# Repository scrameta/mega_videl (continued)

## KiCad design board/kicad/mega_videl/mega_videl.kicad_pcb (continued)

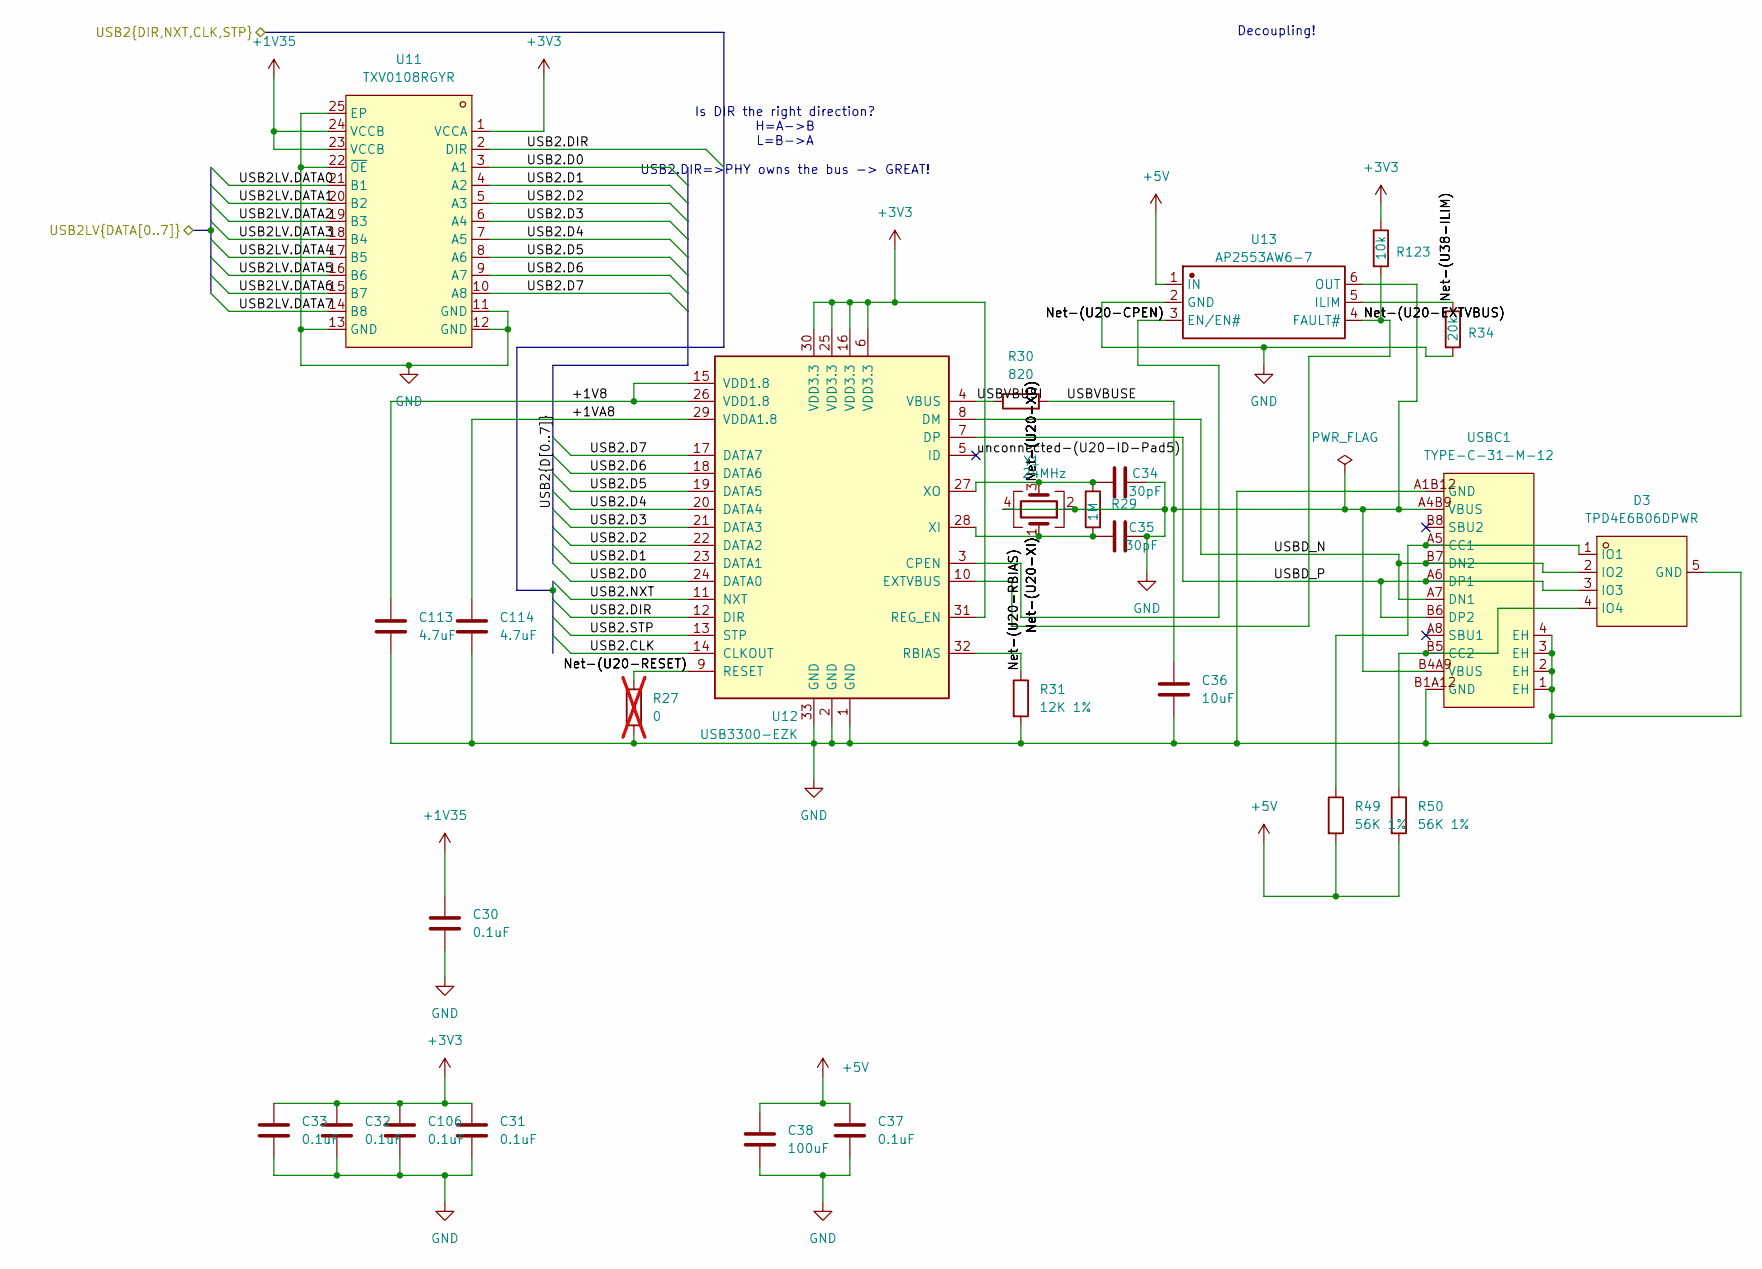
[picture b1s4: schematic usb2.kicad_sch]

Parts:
C30, C31, C32, C33, C37, C106: 0.1uF; C_0603_1608Metric; LCSC C14663
C34, C35: 30pF; C_0603_1608Metric; LCSC C1658
C36: 10uF; C_0805_2012Metric; LCSC C15850
C38: 100uF; C_1206_3216Metric; LCSC C7432784
C113, C114: 4.7uF; C_0805_2012Metric; LCSC C1779
D3: TPD4E6B06DPWR; X2SON-4_L0.8-W0.8-P0.48-TL-A; MPN TPD4E6B06DPWR; LCSC Part C2869397
R27: 0; R_0603_1608Metric; LCSC C21189; not fitted
R29: 1M; R_0603_1608Metric; LCSC C22935
R30: 820; R_0603_1608Metric; LCSC C23253
R31: 12K 1%; R_0603_1608Metric; LCSC C22790
R34: 20k; R_0603_1608Metric; LCSC C4184
R49, R50: 56K 1%; R_0603_1608Metric; LCSC C23206
R123: 10k; R_0603_1608Metric; LCSC C25804
U11: TXV0108RGYR; TQFN-24_L5.5-W3.5-P0.50-BR-EP; MPN TXV0108RGYR; LCSC Part C22428389
U12: USB3300-EZK; QFN-32-1EP_5x5mm_P0.5mm_EP3.45x3.45mm; LCSC C108383
U13: AP2553AW6-7; SOT-26_L3.0-W1.6-P0.95-LS2.8-BL; Manufacturer Part AP2553AW6-7; JLC_3DModel df0aaac1b0f04609b13717eddf3d6f89
USBC1: TYPE-C-31-M-12; USB-C_SMD-TYPE-C-31-M-12_1; MPN TYPE-C-31-M-12; LCSC Part C165948
Y1: 24MHz; Crystal_SMD_3225-4Pin_3.2x2.5mm; LCSC C5308006

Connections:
+1V35: C30.1, U11.23 (VCCB), U11.24 (VCCB); also elsewhere on the board
+3V3: C31.1, C32.1, C33.1, C106.1, R123.1, U11.1 (VCCA), U12.6 (VDD3.3), U12.16 (VDD3.3), U12.25 (VDD3.3), U12.30 (VDD3.3), U12.31 (REG_EN); also elsewhere on the board
+5V: C37.1, C38.1, R49.2, R50.2, U13.1 (IN); also elsewhere on the board
/fpga/USB2.CLK: U12.14 (CLKOUT); also elsewhere on the board
/fpga/USB2.DIR: U11.2 (DIR), U12.12 (DIR); also elsewhere on the board
/fpga/USB2.NXT: U12.11 (NXT); also elsewhere on the board
/fpga/USB2.STP: U12.13 (STP); also elsewhere on the board
/fpga/USB2LV.DATA0: U11.21 (B1); also elsewhere on the board
/fpga/USB2LV.DATA1: U11.20 (B2); also elsewhere on the board
/fpga/USB2LV.DATA2: U11.19 (B3); also elsewhere on the board
/fpga/USB2LV.DATA3: U11.18 (B4); also elsewhere on the board
/fpga/USB2LV.DATA4: U11.17 (B5); also elsewhere on the board
/fpga/USB2LV.DATA5: U11.16 (B6); also elsewhere on the board
/fpga/USB2LV.DATA6: U11.15 (B7); also elsewhere on the board
/fpga/USB2LV.DATA7: U11.14 (B8); also elsewhere on the board
/usb2/+1V8: C113.1, U12.15 (VDD1.8), U12.26 (VDD1.8)
/usb2/+1VA8: C114.1, U12.29 (VDDA1.8)
/usb2/Net-(U20-CPEN): U12.3 (CPEN), U13.3 (EN/EN#)
/usb2/Net-(U20-EXTVBUS): R123.2, U12.10 (EXTVBUS), U13.4 (FAULT#)
/usb2/Net-(U20-RBIAS): R31.1, U12.32 (RBIAS)
/usb2/Net-(U20-RESET): R27.1, U12.9 (RESET)
/usb2/Net-(U20-XI): C35.2, R29.2, U12.28 (XI), Y1.1
/usb2/Net-(U20-XO): C34.2, R29.1, U12.27 (XO), Y1.3
/usb2/Net-(U38-ILIM): R34.1, U13.5 (ILIM)
/usb2/USB2.D0: U11.3 (A1), U12.24 (DATA0)
/usb2/USB2.D1: U11.4 (A2), U12.23 (DATA1)
/usb2/USB2.D2: U11.5 (A3), U12.22 (DATA2)
/usb2/USB2.D3: U11.6 (A4), U12.21 (DATA3)
/usb2/USB2.D4: U11.7 (A5), U12.20 (DATA4)
/usb2/USB2.D5: U11.8 (A6), U12.19 (DATA5)
/usb2/USB2.D6: U11.9 (A7), U12.18 (DATA6)
/usb2/USB2.D7: U11.10 (A8), U12.17 (DATA7)
/usb2/USBD_N: D3.2 (IO2), U12.8 (DM), USBC1.A7 (DN1), USBC1.B7 (DN2)
/usb2/USBD_P: D3.3 (IO3), U12.7 (DP), USBC1.A6 (DP1), USBC1.B6 (DP2)
/usb2/USBVBUSE: C36.1, R30.2, U13.6 (OUT), USBC1.A4B9 (VBUS), USBC1.B4A9 (VBUS)
/usb2/USBVBUSI: R30.1, U12.4 (VBUS)
/usb2/unconnected-(U20-ID-Pad5): U12.5 (ID)
GND: C30.2, C31.2, C32.2, C33.2, C34.1, C35.1, C36.2, C37.2, C38.2, C106.2, C113.2, C114.2, D3.5 (GND), R27.2, R31.2, R34.2, U11.11 (GND), U11.12 (GND), U11.13 (GND), U11.22 (~OE), U11.25 (EP), U12.1 (GND), U12.2 (GND), U12.33 (GND), U13.2 (GND), USBC1.1 (EH), USBC1.2 (EH), USBC1.3 (EH), USBC1.4 (EH), USBC1.A1B12 (GND), USBC1.B1A12 (GND), Y1.2, Y1.4; also elsewhere on the board
unnamed: D3.1 (IO1), R49.1, USBC1.A5 (CC1)
unnamed: D3.4 (IO4), R50.1, USBC1.B5 (CC2)

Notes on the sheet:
Is DIR the right direction? H=A->B L=B->A USB2.DIR=>PHY owns the bus -> GREAT!
Decoupling!

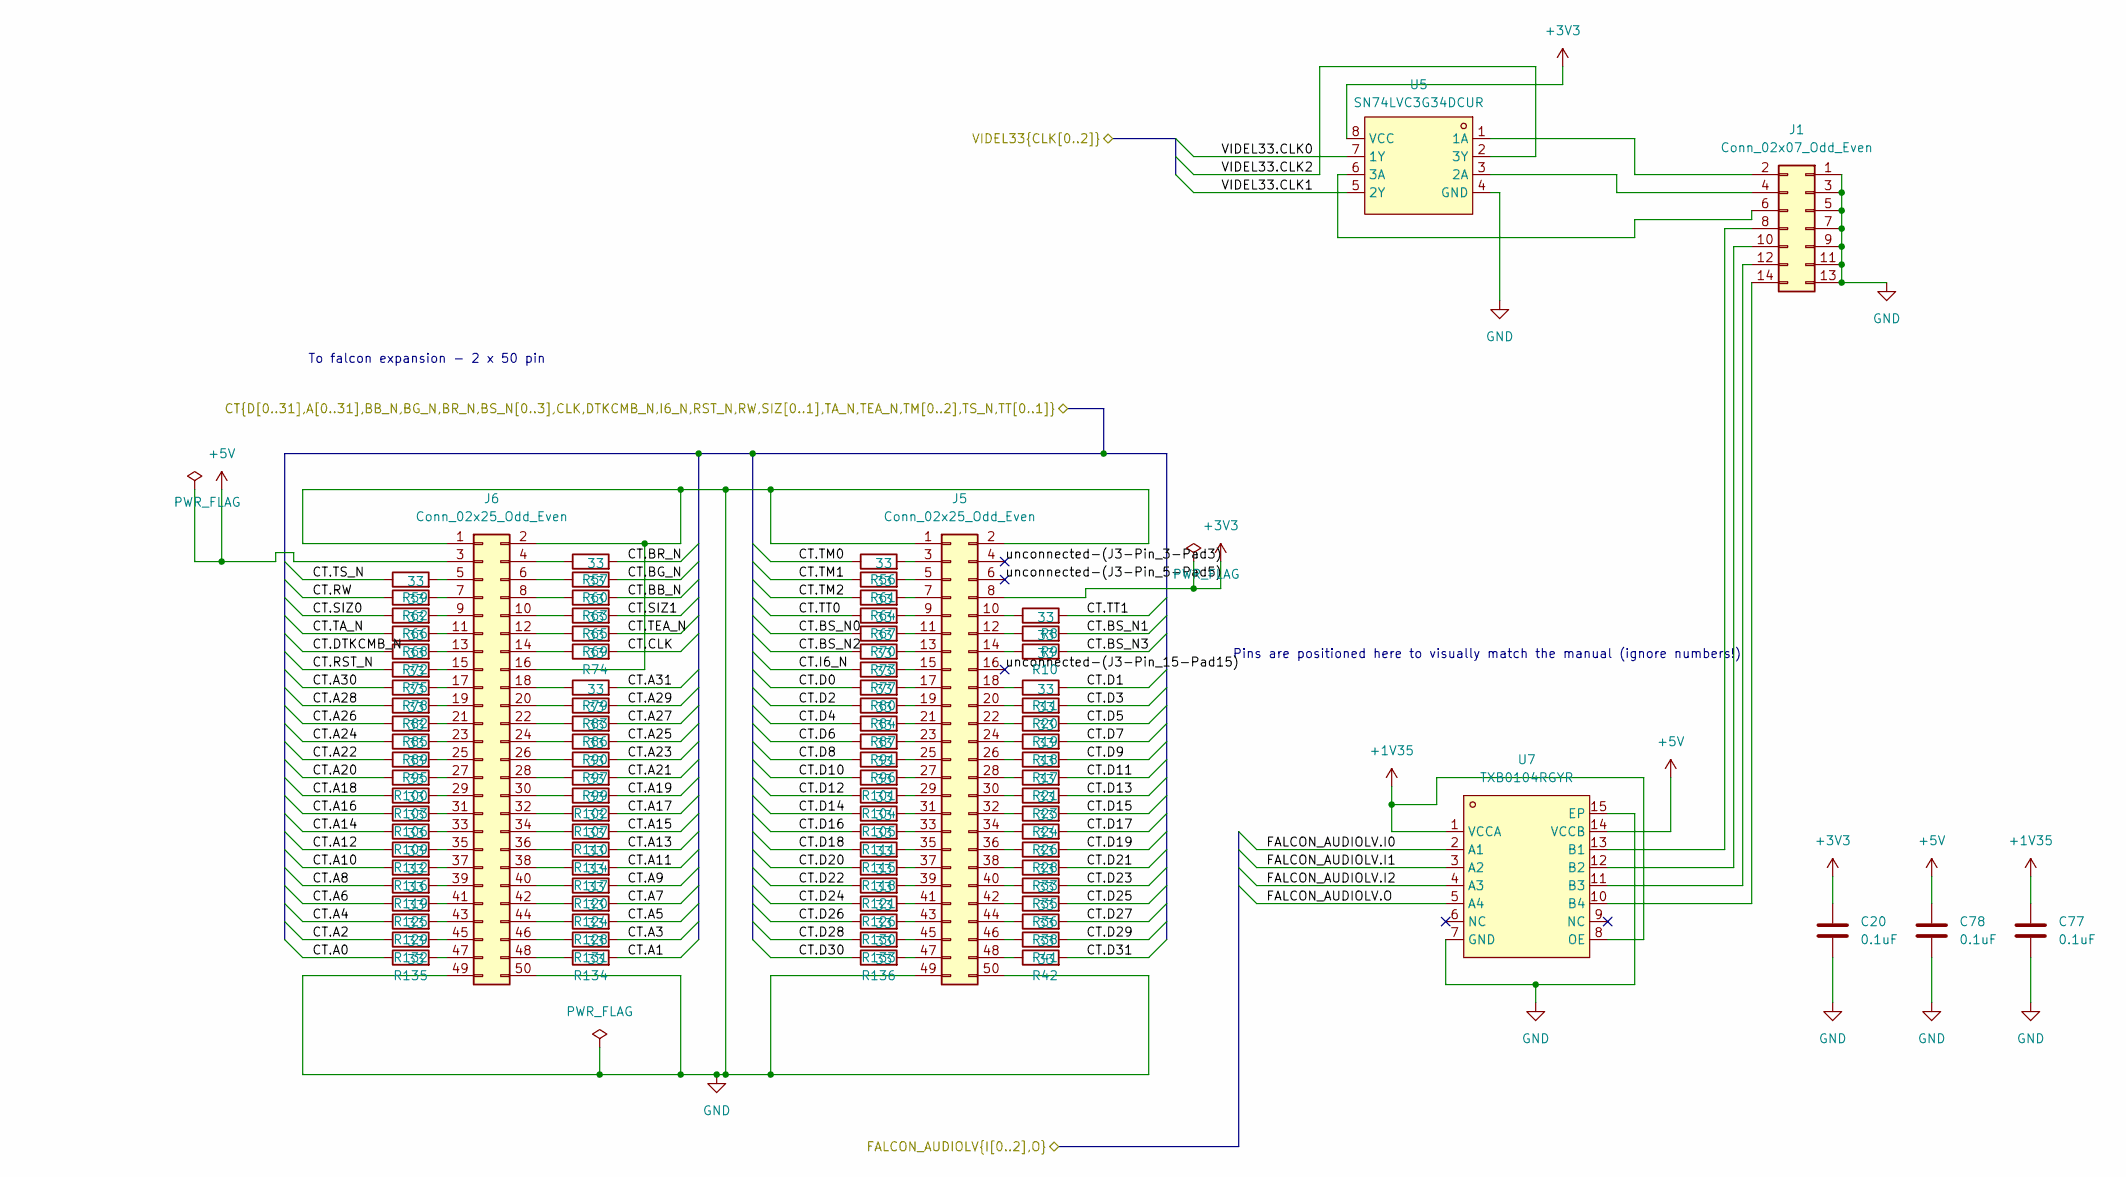
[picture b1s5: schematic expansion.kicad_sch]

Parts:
C20, C77, C78: 0.1uF; C_0603_1608Metric; LCSC C14663
J1: Conn_02x07_Odd_Even; PinHeader_2x07_P2.54mm_Vertical_SMD; LCSC C7366128
J5, J6: Conn_02x25_Odd_Even; PinSocket_2x25_P2.54mm_Vertical_SMD; LCSC C52611
R8, R9, R10, R11, R17, R18, R19, R20, R21, R23, R24, R26, R28, R33, R35, R36, R38, R41, R42, R56, R57, R59, R60, R61, R62, R63, R64, R65, R66, R67, R68, R69, R70, R72, R73, R74, R75, R77, R78, R79, R80, R82, R83, R84, R85, R86, R87, R89, R90, R91, R95, R96, R97, R99, R100, R101, R102, R103, R104, R105, R106, R107, R109, R110, R111, R112, R114, R115, R116, R117, R118, R119, R120, R121, R124, R125, R126, R128, R129, R130, R131, R132, R133, R134, R135, R136: 33; R_0402_1005Metric; LCSC C25105
U5: SN74LVC3G34DCUR; VSSOP-8_L2.1-W2.4-P0.50-LS3.2-BR; MPN SN74LVC3G34DCUR; LCSC Part C130024
U7: TXB0104RGYR; VQFN-14_L3.5-W3.5-P0.50-BL-EP; MPN TXB0104RGYR; LCSC Part C400708

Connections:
+1V35: C77.1, U7.1 (VCCA), U7.8 (OE); also elsewhere on the board
+3V3: C20.1, J5.8, U5.8 (VCC); also elsewhere on the board
+5V: C78.1, J6.3, U7.14 (VCCB); also elsewhere on the board
/expansion/unconnected-(J3-Pin_3-Pad3): J5.4
/expansion/unconnected-(J3-Pin_5-Pad5): J5.6
/expansion/unconnected-(J3-Pin_15-Pad15): J5.16
/fpga/CT.A0: R135.1; also elsewhere on the board
/fpga/CT.A1: R134.2; also elsewhere on the board
/fpga/CT.A2: R132.1; also elsewhere on the board
/fpga/CT.A3: R131.2; also elsewhere on the board
/fpga/CT.A4: R129.1; also elsewhere on the board
/fpga/CT.A5: R128.2; also elsewhere on the board
/fpga/CT.A6: R125.1; also elsewhere on the board
/fpga/CT.A7: R124.2; also elsewhere on the board
/fpga/CT.A8: R119.1; also elsewhere on the board
/fpga/CT.A9: R120.2; also elsewhere on the board
/fpga/CT.A10: R116.1; also elsewhere on the board
/fpga/CT.A11: R117.2; also elsewhere on the board
/fpga/CT.A12: R112.1; also elsewhere on the board
/fpga/CT.A13: R114.2; also elsewhere on the board
/fpga/CT.A14: R109.1; also elsewhere on the board
/fpga/CT.A15: R110.2; also elsewhere on the board
/fpga/CT.A16: R106.1; also elsewhere on the board
/fpga/CT.A17: R107.2; also elsewhere on the board
/fpga/CT.A18: R103.1; also elsewhere on the board
/fpga/CT.A19: R102.2; also elsewhere on the board
/fpga/CT.A20: R100.1; also elsewhere on the board
/fpga/CT.A21: R99.2; also elsewhere on the board
/fpga/CT.A22: R95.1; also elsewhere on the board
/fpga/CT.A23: R97.2; also elsewhere on the board
/fpga/CT.A24: R89.1; also elsewhere on the board
/fpga/CT.A25: R90.2; also elsewhere on the board
/fpga/CT.A26: R85.1; also elsewhere on the board
/fpga/CT.A27: R86.2; also elsewhere on the board
/fpga/CT.A28: R82.1; also elsewhere on the board
/fpga/CT.A29: R83.2; also elsewhere on the board
/fpga/CT.A30: R78.1; also elsewhere on the board
/fpga/CT.A31: R79.2; also elsewhere on the board
/fpga/CT.BB_N: R63.2; also elsewhere on the board
/fpga/CT.BG_N: R60.2; also elsewhere on the board
/fpga/CT.BR_N: R57.2; also elsewhere on the board
/fpga/CT.BS_N0: R70.1; also elsewhere on the board
/fpga/CT.BS_N1: R9.2; also elsewhere on the board
/fpga/CT.BS_N2: R73.1; also elsewhere on the board
/fpga/CT.BS_N3: R10.2; also elsewhere on the board
/fpga/CT.CLK: R74.2; also elsewhere on the board
/fpga/CT.D0: R80.1; also elsewhere on the board
/fpga/CT.D1: R11.2; also elsewhere on the board
/fpga/CT.D2: R84.1; also elsewhere on the board
/fpga/CT.D3: R20.2; also elsewhere on the board
/fpga/CT.D4: R87.1; also elsewhere on the board
/fpga/CT.D5: R19.2; also elsewhere on the board
/fpga/CT.D6: R91.1; also elsewhere on the board
/fpga/CT.D7: R18.2; also elsewhere on the board
/fpga/CT.D8: R96.1; also elsewhere on the board
/fpga/CT.D9: R17.2; also elsewhere on the board
/fpga/CT.D10: R101.1; also elsewhere on the board
/fpga/CT.D11: R21.2; also elsewhere on the board
/fpga/CT.D12: R104.1; also elsewhere on the board
/fpga/CT.D13: R23.2; also elsewhere on the board
/fpga/CT.D14: R105.1; also elsewhere on the board
/fpga/CT.D15: R24.2; also elsewhere on the board
/fpga/CT.D16: R111.1; also elsewhere on the board
/fpga/CT.D17: R26.2; also elsewhere on the board
/fpga/CT.D18: R115.1; also elsewhere on the board
/fpga/CT.D19: R28.2; also elsewhere on the board
/fpga/CT.D20: R118.1; also elsewhere on the board
/fpga/CT.D21: R33.2; also elsewhere on the board
/fpga/CT.D22: R121.1; also elsewhere on the board
/fpga/CT.D23: R35.2; also elsewhere on the board
/fpga/CT.D24: R126.1; also elsewhere on the board
/fpga/CT.D25: R36.2; also elsewhere on the board
/fpga/CT.D26: R130.1; also elsewhere on the board
/fpga/CT.D27: R38.2; also elsewhere on the board
/fpga/CT.D28: R133.1; also elsewhere on the board
/fpga/CT.D29: R41.2; also elsewhere on the board
/fpga/CT.D30: R136.1; also elsewhere on the board
/fpga/CT.D31: R42.2; also elsewhere on the board
/fpga/CT.DTKCMB_N: R72.1; also elsewhere on the board
/fpga/CT.I6_N: R77.1; also elsewhere on the board
/fpga/CT.RST_N: R75.1; also elsewhere on the board
/fpga/CT.RW: R62.1; also elsewhere on the board
/fpga/CT.SIZ0: R66.1; also elsewhere on the board
/fpga/CT.SIZ1: R65.2; also elsewhere on the board
/fpga/CT.TA_N: R68.1; also elsewhere on the board
/fpga/CT.TEA_N: R69.2; also elsewhere on the board
/fpga/CT.TM0: R56.1; also elsewhere on the board
/fpga/CT.TM1: R61.1; also elsewhere on the board
/fpga/CT.TM2: R64.1; also elsewhere on the board
/fpga/CT.TS_N: R59.1; also elsewhere on the board
/fpga/CT.TT0: R67.1; also elsewhere on the board
/fpga/CT.TT1: R8.2; also elsewhere on the board
/fpga/FALCON_AUDIOLV.I0: U7.2 (A1); also elsewhere on the board
/fpga/FALCON_AUDIOLV.I1: U7.3 (A2); also elsewhere on the board
/fpga/FALCON_AUDIOLV.I2: U7.4 (A3); also elsewhere on the board
/fpga/FALCON_AUDIOLV.O: U7.5 (A4); also elsewhere on the board
/fpga/VIDEL33.CLK0: U5.7 (1Y); also elsewhere on the board
/fpga/VIDEL33.CLK1: U5.5 (2Y); also elsewhere on the board
/fpga/VIDEL33.CLK2: U5.2 (3Y); also elsewhere on the board
GND: C20.2, C77.2, C78.2, J1.1, J1.3, J1.5, J1.7, J1.9, J1.11, J1.13, J5.1, J5.2, J5.49, J5.50, J6.1, J6.2, J6.16, J6.49, J6.50, U5.4 (GND), U7.7 (GND), U7.15 (EP); also elsewhere on the board
unnamed: J1.2, U5.1 (1A)
unnamed: J1.4, U5.3 (2A)
unnamed: J1.6, U5.6 (3A)
unnamed: J1.8, U7.13 (B1)
unnamed: J1.10, U7.12 (B2)
unnamed: J1.12, U7.11 (B3)
unnamed: J1.14, U7.10 (B4)
unnamed: J5.3, R56.2
unnamed: J5.5, R61.2
unnamed: J5.7, R64.2
unnamed: J5.9, R67.2
unnamed: J5.10, R8.1
unnamed: J5.11, R70.2
unnamed: J5.12, R9.1
unnamed: J5.13, R73.2
unnamed: J5.14, R10.1
unnamed: J5.15, R77.2
unnamed: J5.17, R80.2
unnamed: J5.18, R11.1
unnamed: J5.19, R84.2
unnamed: J5.20, R20.1
unnamed: J5.21, R87.2
unnamed: J5.22, R19.1
unnamed: J5.23, R91.2
unnamed: J5.24, R18.1
unnamed: J5.25, R96.2
unnamed: J5.26, R17.1
unnamed: J5.27, R101.2
unnamed: J5.28, R21.1
unnamed: J5.29, R104.2
unnamed: J5.30, R23.1
unnamed: J5.31, R105.2
unnamed: J5.32, R24.1
unnamed: J5.33, R111.2
unnamed: J5.34, R26.1
unnamed: J5.35, R115.2
unnamed: J5.36, R28.1
unnamed: J5.37, R118.2
unnamed: J5.38, R33.1
unnamed: J5.39, R121.2
unnamed: J5.40, R35.1
unnamed: J5.41, R126.2
unnamed: J5.42, R36.1
unnamed: J5.43, R130.2
unnamed: J5.44, R38.1
unnamed: J5.45, R133.2
unnamed: J5.46, R41.1
unnamed: J5.47, R136.2
unnamed: J5.48, R42.1
unnamed: J6.4, R57.1
unnamed: J6.5, R59.2
unnamed: J6.6, R60.1
unnamed: J6.7, R62.2
unnamed: J6.8, R63.1
unnamed: J6.9, R66.2
unnamed: J6.10, R65.1
unnamed: J6.11, R68.2
unnamed: J6.12, R69.1
unnamed: J6.13, R72.2
unnamed: J6.14, R74.1
unnamed: J6.15, R75.2
unnamed: J6.17, R78.2
unnamed: J6.18, R79.1
unnamed: J6.19, R82.2
unnamed: J6.20, R83.1
unnamed: J6.21, R85.2
unnamed: J6.22, R86.1
unnamed: J6.23, R89.2
unnamed: J6.24, R90.1
unnamed: J6.25, R95.2
unnamed: J6.26, R97.1
unnamed: J6.27, R100.2
unnamed: J6.28, R99.1
unnamed: J6.29, R103.2
unnamed: J6.30, R102.1
unnamed: J6.31, R106.2
unnamed: J6.32, R107.1
unnamed: J6.33, R109.2
unnamed: J6.34, R110.1
unnamed: J6.35, R112.2
unnamed: J6.36, R114.1
unnamed: J6.37, R116.2
unnamed: J6.38, R117.1
unnamed: J6.39, R119.2
unnamed: J6.40, R120.1
unnamed: J6.41, R125.2
unnamed: J6.42, R124.1
unnamed: J6.43, R129.2
unnamed: J6.44, R128.1
unnamed: J6.45, R132.2
unnamed: J6.46, R131.1
unnamed: J6.47, R135.2
unnamed: J6.48, R134.1

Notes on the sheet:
To falcon expansion - 2 x 50 pin
Pins are positioned here to visually match the manual (ignore numbers!)

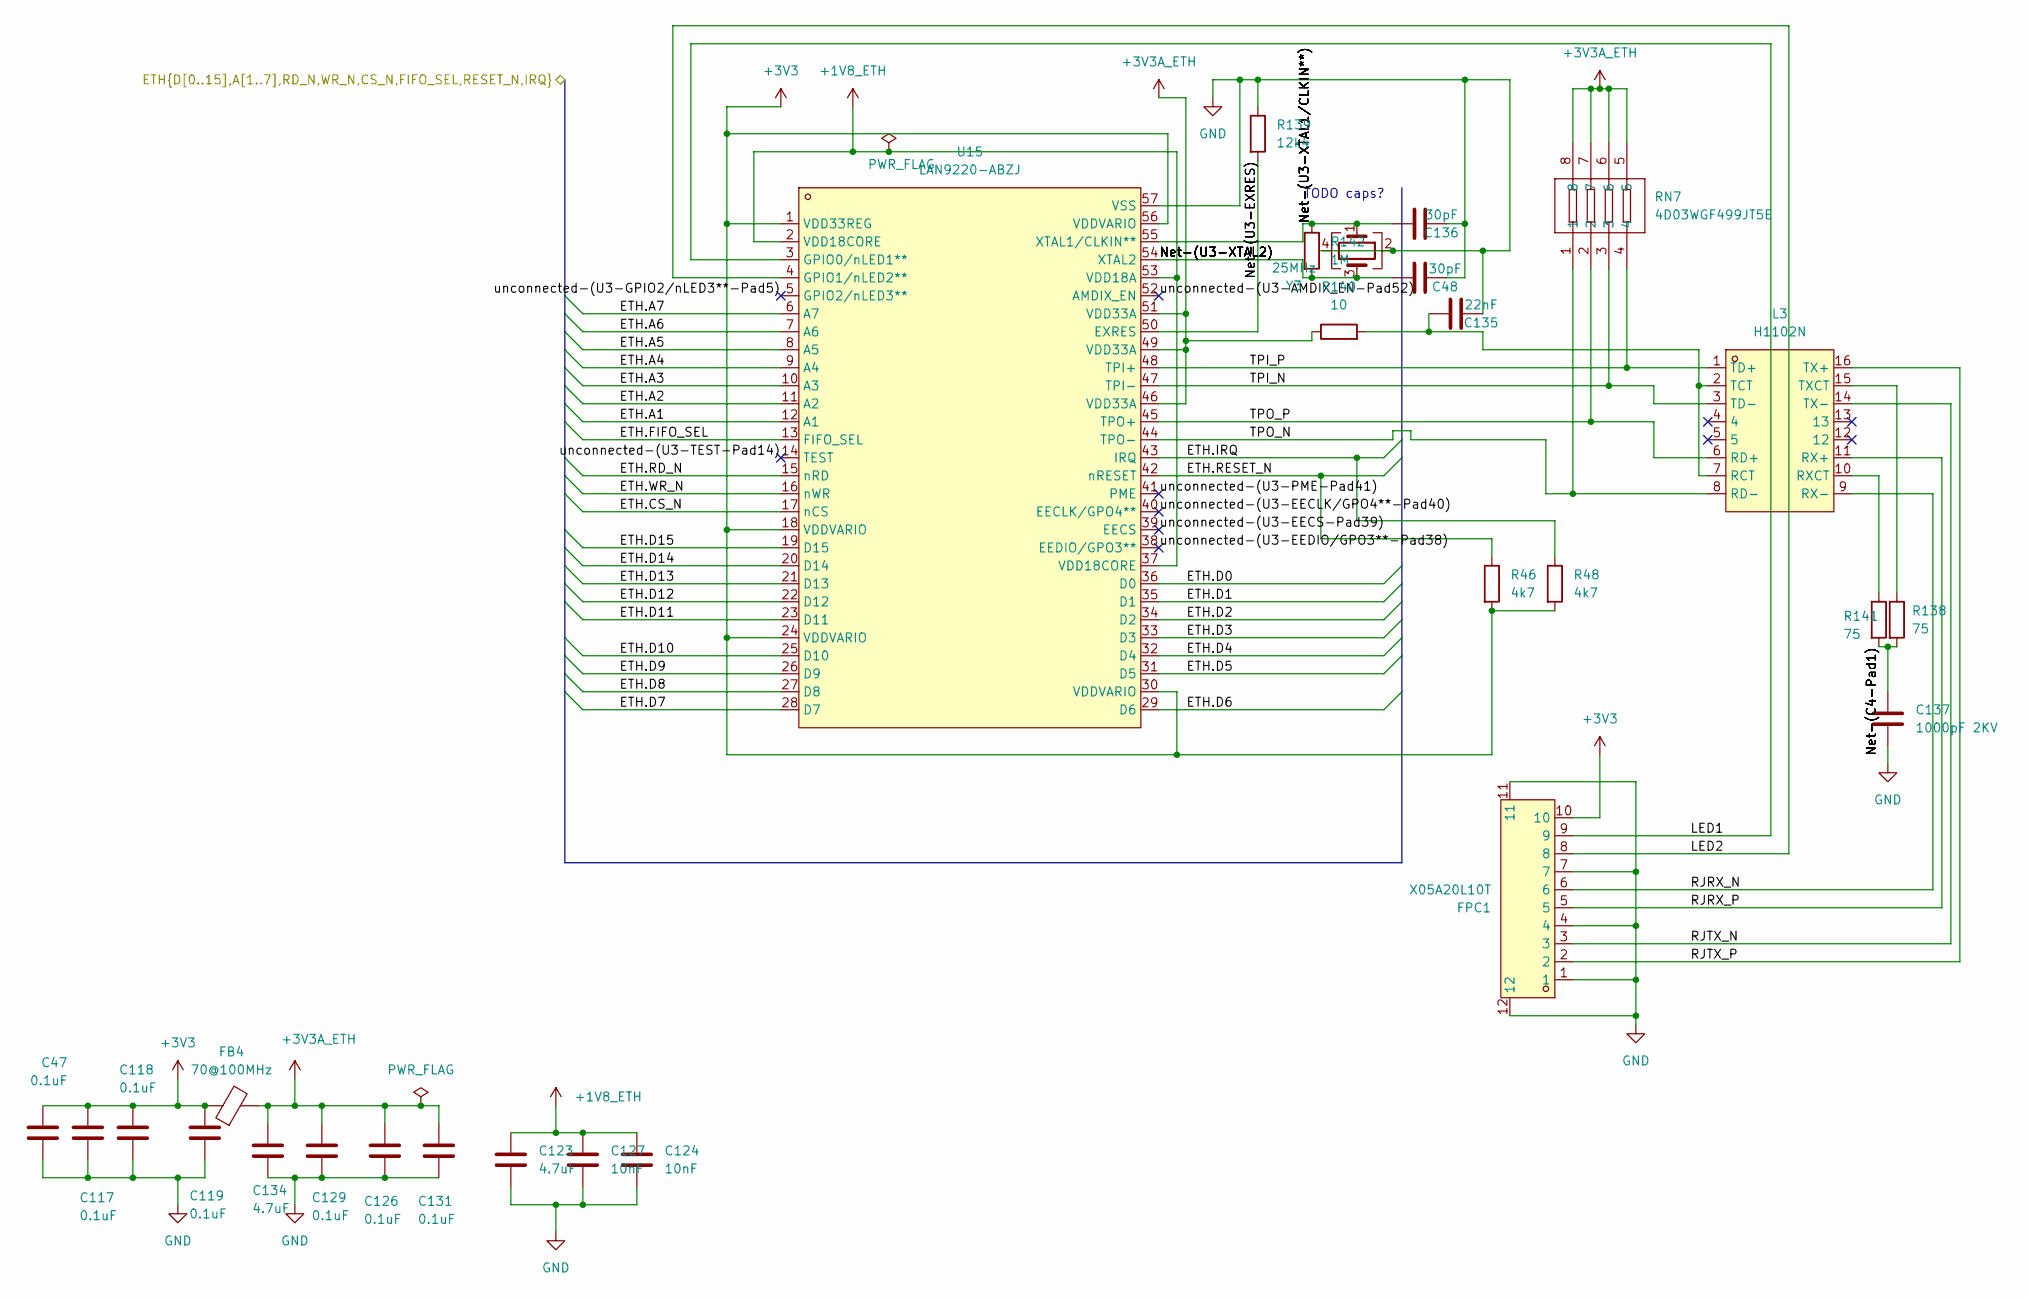
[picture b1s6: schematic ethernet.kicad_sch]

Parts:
C47, C117, C118, C119, C126, C129, C131: 0.1uF; C_0402_1005Metric; LCSC C1525
C48, C136: 30pF; C_0603_1608Metric; LCSC C1658
C123, C134: 4.7uF; C_0805_2012Metric; LCSC C1779
C124, C127: 10nF; C_0402_1005Metric; LCSC C15195
C135: 22nF; C_0603_1608Metric; LCSC C21122
C137: 1000pF 2KV; C_1206_3216Metric; LCSC C9196
FB4: 70@100MHz; L_0805_2012Metric; LCSC C85840
FPC1: X05A20L10T; FFC-SMD_10P-P0.50_X05A20L10T; MPN X05A20L10T; LCSC Part C388667
L3: H1102N; XFMR-SMD_H1102N; MPN H1102N; LCSC Part C42418465
R46, R48: 4k7; R_0603_1608Metric; LCSC C23162
R138, R141: 75; R_0603_1608Metric; LCSC C4275
R139: 12k4; R_0603_1608Metric; LCSC C137798
R140: 10; R_0603_1608Metric; LCSC C22859
R142: 1M; R_0603_1608Metric; LCSC C22935
RN7: 4D03WGF499JT5E; RES-ARRAY-SMD_0603-8P-L3.2-W1.6-BL; MPN 4D03WGF499JT5E; LCSC Part C54832
U15: LAN9220-ABZJ; QFN-56_L8.0-W8.0-P0.50-BL-EP6.0; MPN LAN9220-ABZJ; LCSC Part C1521597
Y3: 25MHz; Crystal_SMD_3225-4Pin_3.2x2.5mm; LCSC C5308007

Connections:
+1V8_ETH: C123.1, C124.1, C127.1, U15.2 (VDD18CORE), U15.37 (VDD18CORE), U15.53 (VDD18A)
+3V3: C47.1, C117.1, C118.1, C119.1, FB4.1, FPC1.10, R46.2, R48.2, U15.1 (VDD33REG), U15.18 (VDDVARIO), U15.24 (VDDVARIO), U15.30 (VDDVARIO), U15.56 (VDDVARIO); also elsewhere on the board
+3V3A_ETH: C126.1, C129.1, C131.1, C134.1, FB4.2, R140.1, RN7.5, RN7.6, RN7.7, RN7.8, U15.46 (VDD33A), U15.49 (VDD33A), U15.51 (VDD33A)
/Ethernet/LED1: FPC1.9, U15.3 (GPIO0/nLED1**)
/Ethernet/LED2: FPC1.8, U15.4 (GPIO1/nLED2**)
/Ethernet/Net-(C4-Pad1): C137.1, R138.2, R141.2
/Ethernet/Net-(U3-EXRES): R139.2, U15.50 (EXRES)
/Ethernet/Net-(U3-XTAL1/CLKIN**): C136.2, R142.1, U15.55 (XTAL1/CLKIN**), Y3.1
/Ethernet/Net-(U3-XTAL2): C48.2, R142.2, U15.54 (XTAL2), Y3.3
/Ethernet/RJRX_N: FPC1.6, L3.9 (RX-)
/Ethernet/RJRX_P: FPC1.5, L3.11 (RX+)
/Ethernet/RJTX_N: FPC1.3, L3.14 (TX-)
/Ethernet/RJTX_P: FPC1.2, L3.16 (TX+)
/Ethernet/TPI_N: L3.3 (TD-), RN7.3, U15.47 (TPI-)
/Ethernet/TPI_P: L3.1 (TD+), RN7.4, U15.48 (TPI+)
/Ethernet/TPO_N: L3.8 (RD-), RN7.1, U15.44 (TPO-)
/Ethernet/TPO_P: L3.6 (RD+), RN7.2, U15.45 (TPO+)
/Ethernet/unconnected-(U3-AMDIX_EN-Pad52): U15.52 (AMDIX_EN)
/Ethernet/unconnected-(U3-EECLK/GPO4**-Pad40): U15.40 (EECLK/GPO4**)
/Ethernet/unconnected-(U3-EECS-Pad39): U15.39 (EECS)
/Ethernet/unconnected-(U3-EEDIO/GPO3**-Pad38): U15.38 (EEDIO/GPO3**)
/Ethernet/unconnected-(U3-GPIO2/nLED3**-Pad5): U15.5 (GPIO2/nLED3**)
/Ethernet/unconnected-(U3-PME-Pad41): U15.41 (PME)
/Ethernet/unconnected-(U3-TEST-Pad14): U15.14 (TEST)
/fpga/ETH.A1: U15.12 (A1); also elsewhere on the board
/fpga/ETH.A2: U15.11 (A2); also elsewhere on the board
/fpga/ETH.A3: U15.10 (A3); also elsewhere on the board
/fpga/ETH.A4: U15.9 (A4); also elsewhere on the board
/fpga/ETH.A5: U15.8 (A5); also elsewhere on the board
/fpga/ETH.A6: U15.7 (A6); also elsewhere on the board
/fpga/ETH.A7: U15.6 (A7); also elsewhere on the board
/fpga/ETH.CS_N: U15.17 (nCS); also elsewhere on the board
/fpga/ETH.D0: U15.36 (D0); also elsewhere on the board
/fpga/ETH.D1: U15.35 (D1); also elsewhere on the board
/fpga/ETH.D2: U15.34 (D2); also elsewhere on the board
/fpga/ETH.D3: U15.33 (D3); also elsewhere on the board
/fpga/ETH.D4: U15.32 (D4); also elsewhere on the board
/fpga/ETH.D5: U15.31 (D5); also elsewhere on the board
/fpga/ETH.D6: U15.29 (D6); also elsewhere on the board
/fpga/ETH.D7: U15.28 (D7); also elsewhere on the board
/fpga/ETH.D8: U15.27 (D8); also elsewhere on the board
/fpga/ETH.D9: U15.26 (D9); also elsewhere on the board
/fpga/ETH.D10: U15.25 (D10); also elsewhere on the board
/fpga/ETH.D11: U15.23 (D11); also elsewhere on the board
/fpga/ETH.D12: U15.22 (D12); also elsewhere on the board
/fpga/ETH.D13: U15.21 (D13); also elsewhere on the board
/fpga/ETH.D14: U15.20 (D14); also elsewhere on the board
/fpga/ETH.D15: U15.19 (D15); also elsewhere on the board
/fpga/ETH.FIFO_SEL: U15.13 (FIFO_SEL); also elsewhere on the board
/fpga/ETH.IRQ: R48.1, U15.43 (IRQ); also elsewhere on the board
/fpga/ETH.RD_N: U15.15 (nRD); also elsewhere on the board
/fpga/ETH.RESET_N: R46.1, U15.42 (nRESET); also elsewhere on the board
/fpga/ETH.WR_N: U15.16 (nWR); also elsewhere on the board
GND: C47.2, C48.1, C117.2, C118.2, C119.2, C123.2, C124.2, C126.2, C127.2, C129.2, C131.2, C134.2, C135.1, C136.1, C137.2, FPC1.1, FPC1.4, FPC1.7, FPC1.11, FPC1.12, R139.1, U15.57 (VSS), Y3.2, Y3.4; also elsewhere on the board
unnamed: C135.2, L3.2 (TCT), L3.7 (RCT), R140.2
unnamed: L3.10 (RXCT), R141.1
unnamed: L3.15 (TXCT), R138.1

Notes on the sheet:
TODO caps?
